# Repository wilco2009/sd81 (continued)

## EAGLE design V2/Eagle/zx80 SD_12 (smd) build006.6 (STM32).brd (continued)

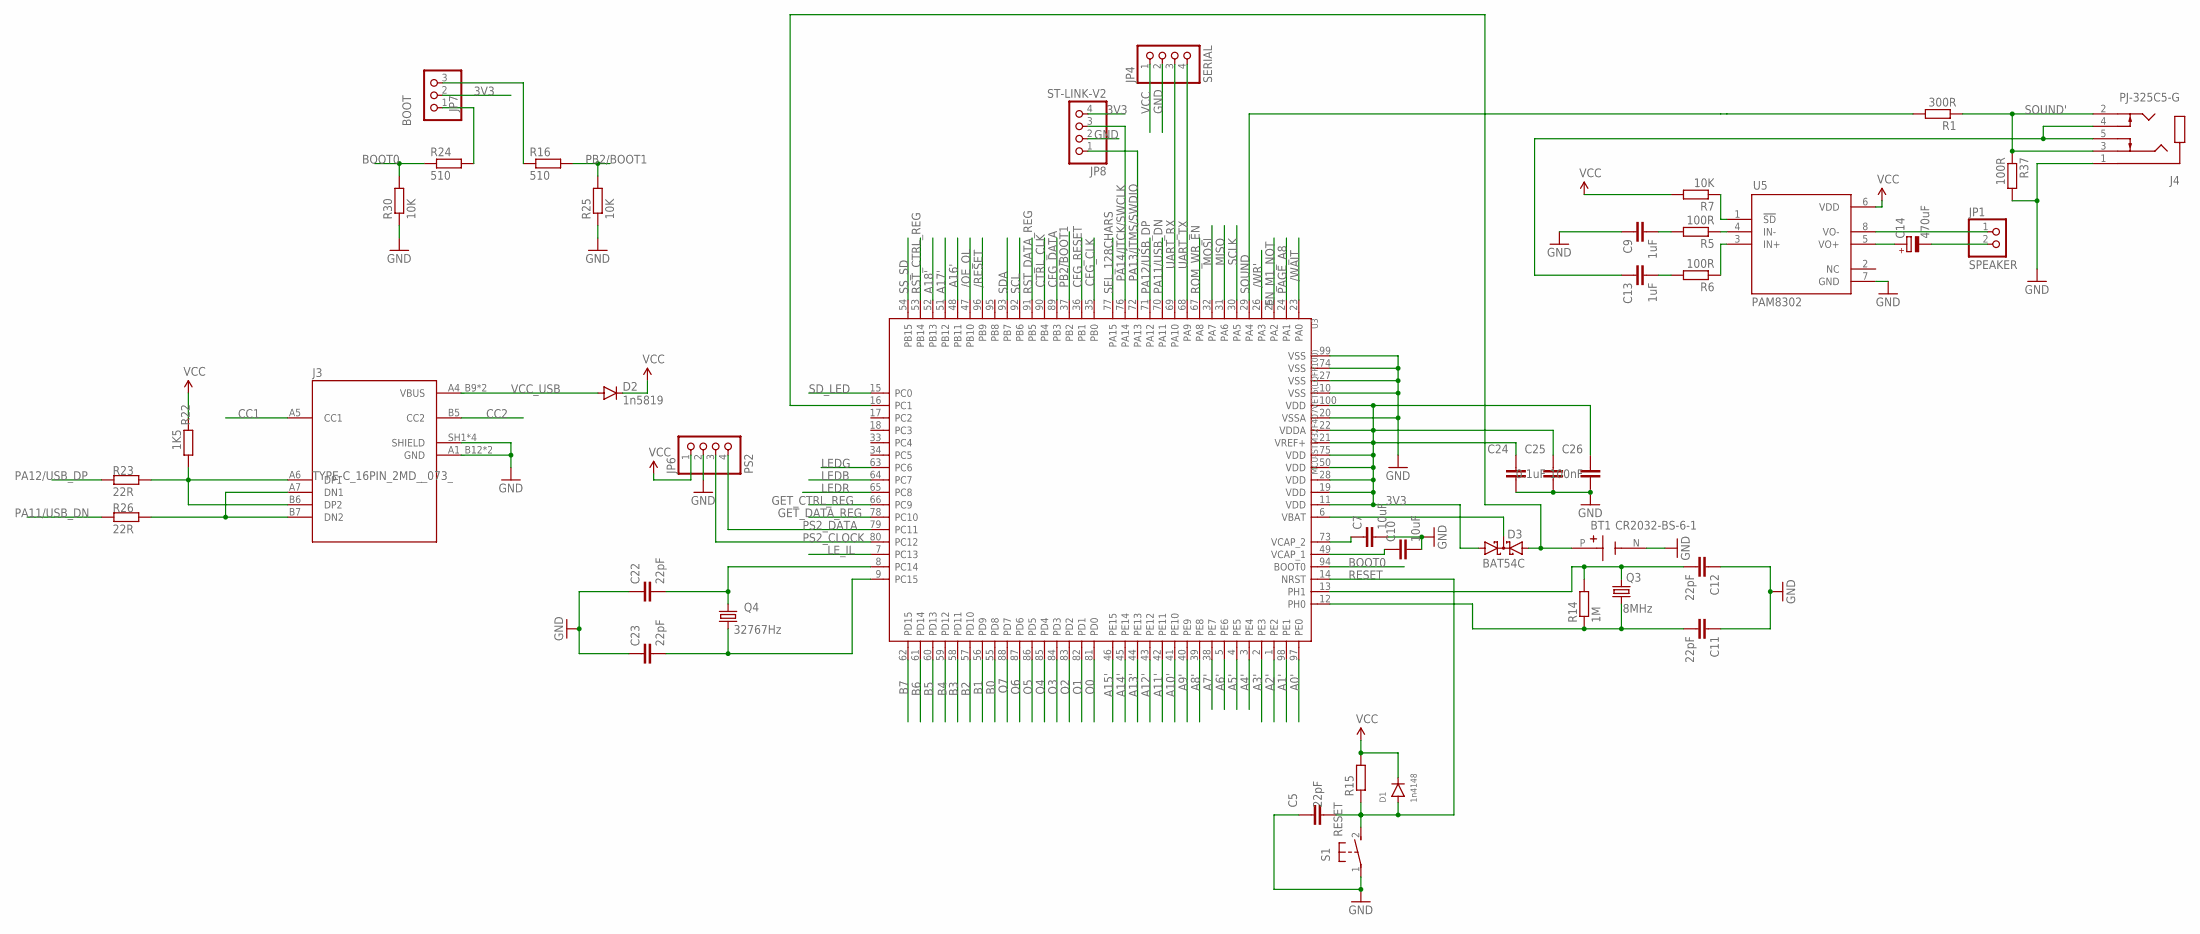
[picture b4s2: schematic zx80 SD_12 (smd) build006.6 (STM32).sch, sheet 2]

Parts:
BT1: CR2032-BS-6-1; BAT_CR2032-BS-6-1
C5, C11, C12, C22, C23: 22pF; C0603
C7, C10: 10uF; C0603
C9, C13: 1uF; C0603
C14: 470uF; UD-6,3X7,7_NICHICON
C24, C25: 0.1uF; C0603
C26: 100nF; C0603
D1: 1n4148; SOD123
D2: 1n5819; SOD323-W
D3: BAT54C; SOT23
J3: TYPE-C_16PIN_2MD__073_; SHOUHAN_TYPE-C_16PIN_2MD__073_
J4: PJ-325C5-G; XKB_PJ-325C5-G
JP1: SPEAKER; 1X02
JP4: SERIAL; 1X04
JP6: PS2; 1X04
JP7: BOOT; 1X03
JP8: ST-LINK-V2; 1X04
Q3: 8MHz; 3.2X2.5_KX-7
Q4: 32767Hz; 3.2X1.5
R1: 300R; R0603
R5, R6, R37: 100R; R0603
R7, R25, R30: 10K; R0603
R14: 1M; R0402
R15: 3k3; R0603
R16, R24: 510; R0603
R22: 1K5; R0603
R23, R26: 22R; R0603
S1: RESET; B3F-31XX
U3: MCU-STM32F407VET6(LQFP100); LQFP100-0.5-13.8X13.8MM
U5: PAM8302; SOIC127P600X170-8N

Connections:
3V3: C24.1, C25.1, C26.1, D3.1 (A1), JP7.2, JP8.4, U3.11 (VDD), U3.19 (VDD), U3.21 (VREF+), U3.22 (VDDA), U3.28 (VDD), U3.50 (VDD), U3.75 (VDD), U3.100 (VDD); also elsewhere on the board
/OE_OL: U3.47 (PB10); also elsewhere on the board
/RESET: U3.96 (PB9); also elsewhere on the board
/WAIT: U3.23 (PA0); also elsewhere on the board
/WR': U3.26 (PA3); also elsewhere on the board
A0': U3.97 (PE0); also elsewhere on the board
A1': U3.98 (PE1); also elsewhere on the board
A2': U3.1 (PE2); also elsewhere on the board
A3': U3.2 (PE3); also elsewhere on the board
A4': U3.3 (PE4); also elsewhere on the board
A5': U3.4 (PE5); also elsewhere on the board
A6': U3.5 (PE6); also elsewhere on the board
A7': U3.38 (PE7); also elsewhere on the board
A8': U3.39 (PE8); also elsewhere on the board
A9': U3.40 (PE9); also elsewhere on the board
A10': U3.41 (PE10); also elsewhere on the board
A11': U3.42 (PE11); also elsewhere on the board
A12': U3.43 (PE12); also elsewhere on the board
A13': U3.44 (PE13); also elsewhere on the board
A14': U3.45 (PE14); also elsewhere on the board
A15': U3.46 (PE15); also elsewhere on the board
A16': U3.48 (PB11); also elsewhere on the board
A17': U3.51 (PB12); also elsewhere on the board
A18': U3.52 (PB13); also elsewhere on the board
B0: U3.55 (PD8); also elsewhere on the board
B1: U3.56 (PD9); also elsewhere on the board
B2: U3.57 (PD10); also elsewhere on the board
B3: U3.58 (PD11); also elsewhere on the board
B4: U3.59 (PD12); also elsewhere on the board
B5: U3.60 (PD13); also elsewhere on the board
B6: U3.61 (PD14); also elsewhere on the board
B7: U3.62 (PD15); also elsewhere on the board
BAT: BT1.P (POS), D3.2 (A2), U3.16 (PC1)
BOOT0: R24.1, R30.2, U3.94 (BOOT0)
CC1: J3.A5 (CC1)
CC2: J3.B5 (CC2)
CFG_CLK: U3.35 (PB0); also elsewhere on the board
CFG_DATA: U3.89 (PB3); also elsewhere on the board
CFG_RESET: U3.36 (PB1); also elsewhere on the board
CTRL_CLK: U3.90 (PB4); also elsewhere on the board
EN_M1_NOT: U3.25 (PA2); also elsewhere on the board
GET_CTRL_REG: U3.66 (PC9); also elsewhere on the board
GET_DATA_REG: U3.78 (PC10); also elsewhere on the board
GND: BT1.N (NEG), C5.1, C7.2, C9.1, C10.2, C11.1, C12.1, C22.1, C23.1, C24.2, C25.2, C26.2, J3.A1_B12 (GND), J3.B1_A12 (GND), J3.SH1 (SHIELD), J3.SH2 (SHIELD), J3.SH3 (SHIELD), J3.SH4 (SHIELD), J4.1, JP4.2, JP6.2, JP8.2, R25.1, R30.1, R37.2, S1.1, U3.10 (VSS), U3.20 (VSSA), U3.27 (VSS), U3.74 (VSS), U3.99 (VSS), U5.7 (GND); also elsewhere on the board
LEDB: U3.64 (PC7); also elsewhere on the board
LEDG: U3.63 (PC6); also elsewhere on the board
LEDR: U3.65 (PC8); also elsewhere on the board
LE_IL: U3.7 (PC13); also elsewhere on the board
MISO: U3.31 (PA6); also elsewhere on the board
MOSI: U3.32 (PA7); also elsewhere on the board
unnamed: J3.A6 (DP1), J3.B6 (DP2), R22.1, R23.1
unnamed: D3.3 (CC), U3.6 (VBAT)
unnamed: R6.1, U5.3 (IN+)
unnamed: R5.1, U5.4 (IN-)
unnamed: R7.1, U5.1 (!SD)
unnamed: C7.1, U3.73 (VCAP_2)
unnamed: J3.A7 (DN1), J3.B7 (DN2), R26.1
unnamed: C9.2, R5.2
unnamed: C13.2, R6.2
unnamed: C10.1, U3.49 (VCAP_1)
unnamed: C11.2, Q3.1, R14.1, U3.12 (PH0)
unnamed: C12.2, Q3.3 (2), R14.2, U3.13 (PH1)
unnamed: JP7.3, R16.1
unnamed: JP7.1, R24.2
unnamed: C22.2, Q4.2, U3.8 (PC14)
unnamed: C23.2, Q4.1, U3.9 (PC15)
unnamed: C14.+, U5.5 (VO+)
unnamed: JP1.1, U5.8 (VO-)
unnamed: C13.1, J4.4, J4.5
unnamed: C14.-, JP1.2
O0: U3.81 (PD0); also elsewhere on the board
O1: U3.82 (PD1); also elsewhere on the board
O2: U3.83 (PD2); also elsewhere on the board
O3: U3.84 (PD3); also elsewhere on the board
O4: U3.85 (PD4); also elsewhere on the board
O5: U3.86 (PD5); also elsewhere on the board
O6: U3.87 (PD6); also elsewhere on the board
O7: U3.88 (PD7); also elsewhere on the board
PA11/USB_DN: R26.2, U3.70 (PA11)
PA12/USB_DP: R23.2, U3.71 (PA12)
PA13/JTMS/SWDIO: JP8.1, U3.72 (PA13)
PA14/JTCK/SWCLK: JP8.3, U3.76 (PA14)
PAGE_A8: U3.24 (PA1); also elsewhere on the board
PB2/BOOT1: R16.2, R25.2, U3.37 (PB2)
PS2_CLOCK: JP6.3, U3.80 (PC12)
PS2_DATA: JP6.4, U3.79 (PC11)
RESET: C5.2, D1.A, R15.1, S1.2 (S), U3.14 (NRST)
ROM_WR_EN: U3.67 (PA8); also elsewhere on the board
RST_CTRL_REG: U3.53 (PB14); also elsewhere on the board
RST_DATA_REG: U3.91 (PB5); also elsewhere on the board
SCL: U3.92 (PB6)
SCLK: U3.30 (PA5); also elsewhere on the board
SDA: U3.93 (PB7)
SD_LED: U3.15 (PC0); also elsewhere on the board
SEL_128CHARS: U3.77 (PA15); also elsewhere on the board
SOUND: R1.2, U3.29 (PA4)
SOUND': J4.2, J4.3, R1.1, R37.1; also elsewhere on the board
SS_SD: U3.54 (PB15); also elsewhere on the board
UART_RX: JP4.3, U3.69 (PA10)
UART_TX: JP4.4, U3.68 (PA9)
VCC: D1.C, D2.C, JP4.1, JP6.1, R7.2, R15.2, R22.2, U5.6 (VDD); also elsewhere on the board
VCC_USB: D2.A, J3.A4_B9 (VBUS), J3.B4_A9 (VBUS)

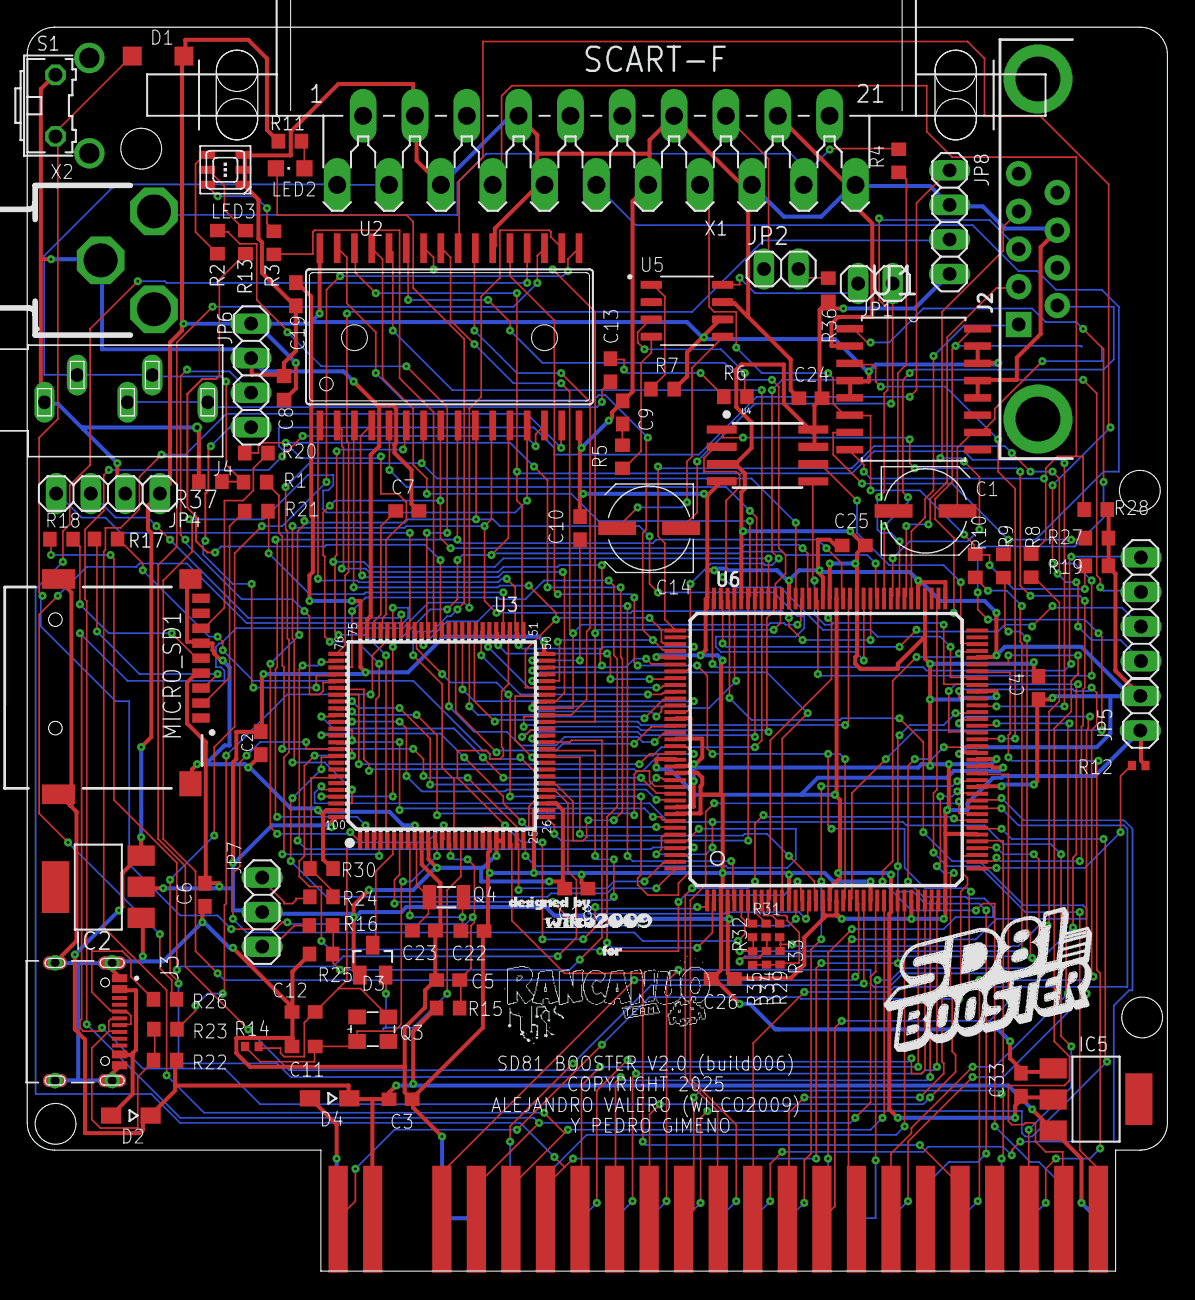
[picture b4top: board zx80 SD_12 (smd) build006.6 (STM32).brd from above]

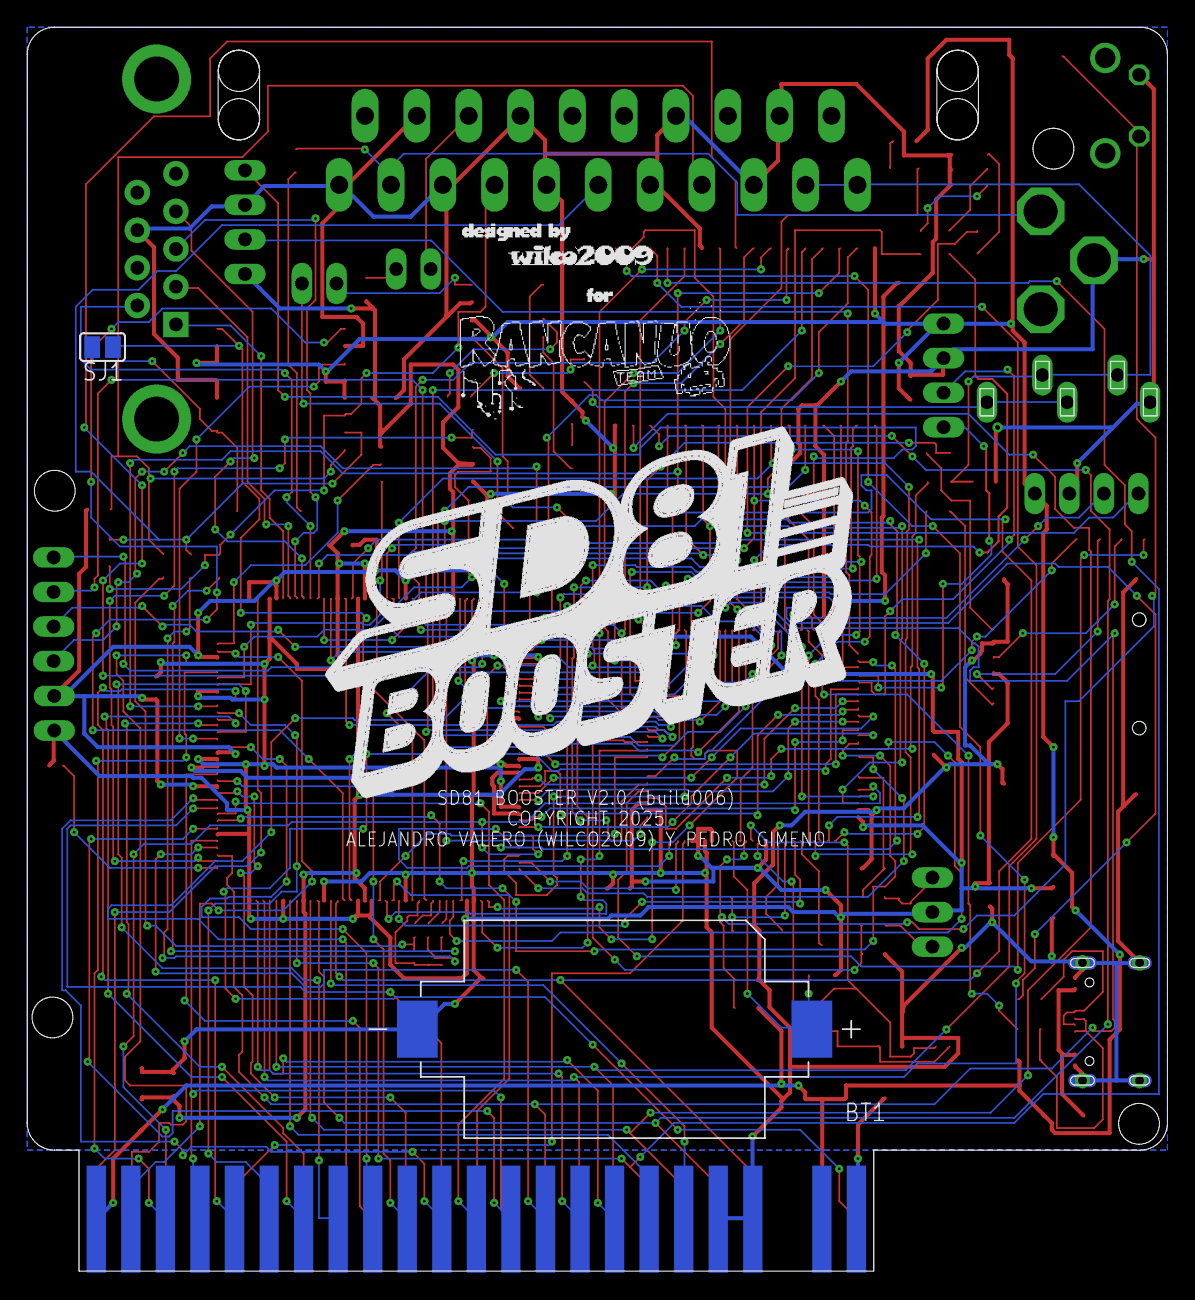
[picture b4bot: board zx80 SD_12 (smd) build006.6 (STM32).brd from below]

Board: 2 copper layers, 83.8 x 91.4 mm, 136 parts (24 on the bottom side), 174 nets.

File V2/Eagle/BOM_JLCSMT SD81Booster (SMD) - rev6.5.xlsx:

Comment | Designator | Footprint | JLCPCB Part #（optional）
220uF | C1 | SMD,D6.3xL7.7mm | C32514
100nF | C2 | C0603 | C14663
10uF | C3 | C0603 | C19702
100nF | C4 | C0603 | C14663
22pF | C5 | C0603 | C1653
10uF | C6 | C0603 | C19702
10uF | C7 | C0603 | C19702
100nF | C8 | C0603 | C14663
1uF | C9 | C0603 | C15849
10uF | C10 | C0603 | C19702
22pF | C11 | C0603 | C1653
22pF | C12 | C0603 | C1653
1uF | C13 | C0603 | C15849
470uF | C14 | SMD,D6.3xL7.7mm | C3354
100nF | C18 | C0603 | C14663
100nF | C19 | C0603 | C14663
22pF | C22 | C0603 | C1653
22pF | C23 | C0603 | C1653
100nF | C24 | C0603 | C14663
100nF | C25 | C0603 | C14663
100nF | C26 | C0603 | C14663
10uF | C33 | C0603 | C19702
1n4148 | D1 | SOD123 | C81598
1n5819 | D2 | SOD323-W | C191023
BAT54C | D3 | SOT23 | C22466350
1n5819 | D4 | SOD323-W | C191023
REG1117 | IC2 | SOT223 | C6186
1,2V | IC5 | SOT223 | C347218
JOYSTICK | J2 | DR9_MALE | C3020655
TYPE-C_16PIN_2MD__073_ | J3 | SHOUHAN_TYPE-C_16PIN_2MD__073_ | C393939
PJ-325C5-G | J4 | XKB_PJ-325C5-G | C2884942
PINH 1x02 | JP1 | 1X02 | C492401
PINH 1x02 | JP2 | 1X02 | C492401
PINH 1x04 | JP3 | 1X04
PINH 1x04 | JP4 | 1X04 | C2691448
PINH 1x02 | JP5 | 1X02
PINH 1x04 | JP6 | 1X04 | C2691448
PINH 1x03 | JP7 | 1X03 | C2937625
PINH 1x04 | JP8 | 1X04 | C2691448
SD | LED2 | CHIPLED_0805 | C2297
STATUS | LED3 | 3535-PLCC6 | C110402
TF-01A | MICRO_SD1 | TF-01A | C22383473
8MHz | Q3 | 3,2X2,5_KX-7 | C403948
32767Hz | Q4 | 3,2X1,5 | C32346
300R | R1 | R0603 | C23025
150 | R2 | R0603 | C22808
68 | R3 | R0603 | C27592
75R | R4 | R0603 | C4275
100R | R5 | R0603 | C22775
100R | R6 | R0603 | C22775
10K | R7 | R0603 | C25804
270 | R8 | R0603 | C22966
270 | R9 | R0603 | C22966
270 | R10 | R0603 | C22966
680 | R11 | R0603 | C23228
2K | R12 | R0402 | C4109
150 | R13 | R0603 | C22808
1M | R14 | R0603 | C409676
3k3 | R15 | R0603 | C22978
510 | R16 | R0603 | C23193
3k3 | R17 | R0603 | C22978
3k3 | R18 | R0603 | C22978
75R | R19 | R0603 | C4275
3k3 | R20 | R0603 | C22978
3k3 | R21 | R0603 | C22978
1K5 | R22 | R0603 | C22843
22R | R23 | R0603 | C23345
510 | R24 | R0603 | C23193
10K | R25 | R0603 | C25804
22R | R26 | R0603 | C23345
75R | R27 | R0603 | C4275
75R | R28 | R0603 | C4275
1K | R29 | R0402 | C11702
10K | R30 | R0603 | C25804
1K | R31 | R0402 | C11702
1K | R32 | R0402 | C11702
2K | R33 | R0402 | C4109
2K | R34 | R0402 | C4109
2K | R35 | R0402 | C4109
100R | R36 | R0603 | C22775
RESET | S1 | B3F-31XX | C231320
AD724 | U1 | SOIC127P1032X265-16N
AS6C4008 | U2 | SOP32-5 | C2952831
MCU-STM32F407VET6(LQFP100) | U3 | LQFP100-0,5-13,8X13,8MM | C28730
W25Q128JVSIQ | U4 | SO08-EIAJ | C97521
PAM8302 | U5 | SOIC127P600X170-8N | C112137
XC6SLX9-2TQG144C | U6 | TQ144 | C27408
SCART-F | X1 | SCART-F
CON-CONRAD_736880-2P | X2 | 3P

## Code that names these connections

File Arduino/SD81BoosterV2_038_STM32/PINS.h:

#define nWAIT           PA0
#define DEBUG_CLOCK     PA1
#define DEBUG_RDY       PA2
#define nWRb            PA3
#define DAC_PIN         PA4       // Pin PA4 para la salida DAC
#define SCLK            PA5
#define MISO            PA6
#define MOSI            PA7
#define nMEM_OEb        PA8
#define UART_TX         PA9
#define UART_RX         PA10
#define WAIT_SERIAL     PA10  // cambiar?
#define USB_DN          PA11
#define USB_DP          PA12
#define SWDIO           PA13
#define SWCLK           PA14
#define SPARE0          PA15    // connected to FPGA
//#define SEL_128CHARS  PA15

#define CFG_CLK         PB0
#define CFG_RESET       PB1
#define BOOT1           PB2
#define CFG_DATA        PB3
#define CTRL_CLK        PB4
#define RST_DATA_REG    PB5
#define FPGA_HSWAPEN    PB5
#define SCL             PB6   // unconnected
#define SDA             PB7   // unconnected
#define FPGA_RESET      PB8
#define Z80_RESET       PB9
#define nOE_OL          PB10
#define A16b            PB11 
#define A17b            PB12 
#define A18b            PB13 
#define RST_CTRL_REG    PB14
#define SEL_SPI_FLASH   PB14  // alternative use while RESET 
#define SS_SD           PB15  

#define SD_LED          PC0
#define VBAT_IN         PC1    // only as reference. see VBAT.cpp
#define FPGA_DONE       PC2
#define FPGA_CFG        PC3
#define UNUSED0         PC4
// #define QSPIN          PC5
#define SPARE2          PC5
#define ST_LED_G        PC6
#define ST_LED_B        PC7
#define ST_LED_R        PC8
#define GET_CTRL_REG    PC9
#define GET_DATA_REG    PC10
#define QSPIN           PC11     
#define PS2_CLOCK       PC12
#define PS2_DATA        PC13
#define CLK_32KH_0      PC14
#define CLK_32KH_1      PC15

#define ioLatch         GPIOD // shared
#define Data            GPIOD // shared

#define Addr            GPIOE
#define A0b             PE0
#define A1b             PE1
#define A2b             PE2
#define A3b             PE3
#define A4b             PE4
#define A5b             PE5
#define A6b             PE6
#define A7b             PE7
#define A8b             PE8
#define A9b             PE9
#define A10b            PE10
#define A11b            PE11
#define A12b            PE12
#define A13b            PE13
#define A14b            PE14
#define A15b            PE15

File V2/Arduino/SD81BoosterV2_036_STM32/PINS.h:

#define ioLatch        GPIOD
#define VBAT_IN        PC1    // only as reference. see VBAT.cpp
#define ST_LED_R       PC8
#define ST_LED_B       PC7
#define ST_LED_G       PC6
#define DEBUG_RDY      PC13
#define FPGA_RESET      PB9
//#define nMEM_LATCH_OE  7
//#define TMS            8
//#define TDI            9
//#define TDO           10
//#define TCK           11
//#define VREF          12
#define RST_CTRL_REG  PB14
#define CTRL_CLK      PB4
#define RST_DATA_REG  PB5
#define GET_CTRL_REG  PC9
#define GET_DATA_REG  PC10
#define nOE_OL        PB10
#define A16b          PB11 
#define A17b          PB12 
#define A18b          PB13 
#define A15b          PE15
#define A14b          PE14
#define A13b          PE13
#define A12b          PE12
#define A11b          PE11
#define A10b          PE10
#define A9b           PE9
#define A8b           PE8
#define A7b           PE7
#define A6b           PE6
#define A5b           PE5
#define A4b           PE4
#define A3b           PE3
#define A2b           PE2
#define A1b           PE1
#define A0b           PE0
//#define nMEM_CE       38
//#define ALE           39
//#define nMEM_OE       40
#define nWAIT         PA0
//#define FULLPAGING    PA1
#define DEBUG_CLOCK   PA1
#define EN_M1_NOT     PA2
#define nWRb          PA3

#define SD_LED        PC0
//#define INT_CHR_TABLE 48
#define SEL_128CHARS  PA15
#define MISO          PA6
#define MOSI          PA7
#define SCLK          PA5
#define SS_SD         PB15  

#define SDA           PB7
#define SCL           PB6

#define CFG_DATA      PB3
#define CFG_RESET     PB1
#define CFG_CLK       PB0

// NOT USED?
#define ROM_WR_EN     PA8 
#define PS2_DATA      PC11
#define PS2_CLOCK     PC12

// CAMBIAR CON NUEVA VERSION
#define WAIT_SERIAL  PA10  // cambiar?
// #define FPGA_M0      PC12  // poner a 1 en el reset  (A4) PS2DATA NARANJA
// #define FPGA_M1      PC11  // poner a 0 en el reset  (A8) PS2CLOCK ROJO
#define Z80_RESET   PC11
#define FPGA_HSWAPEN PB5

// #define OUTPUT_LATCH  PORTD         
// #define INPUT_LATCH   PIND >> 8

// SINONIMOS
#define nMEM_OEb       PA8
#define Data           GPIOD
#define Addr           GPIOE

#define QSPIN          PC12 // Buscar pin libre


//#define D0            22
//#define D1            23
//#define D2            24
//#define D3            25
//#define D4            26
//#define D5            27
//#define D6            28
//#define D7            29

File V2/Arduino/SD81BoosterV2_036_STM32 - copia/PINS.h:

#define ioLatch        GPIOD
#define ST_LED_R       PC8
#define ST_LED_B       PC7
#define ST_LED_G       PC6
#define LE_IL          PC13
#define Z80_RESET      PB9
//#define nMEM_LATCH_OE  7
//#define TMS            8
//#define TDI            9
//#define TDO           10
//#define TCK           11
//#define VREF          12
#define RST_CTRL_REG  PB14
#define CTRL_CLK      PB4
#define RST_DATA_REG  PB5
#define GET_CTRL_REG  PC9
#define GET_DATA_REG  PC10
#define nOE_OL        PB10
#define A16b          PB11 
#define A17b          PB12 
#define A18b          PB13 
#define A15b          PE15
#define A14b          PE14
#define A13b          PE13
#define A12b          PE12
#define A11b          PE11
#define A10b          PE10
#define A9b           PE9
#define A8b           PE8
#define A7b           PE7
#define A6b           PE6
#define A5b           PE5
#define A4b           PE4
#define A3b           PE3
#define A2b           PE2
#define A1b           PE1
#define A0b           PE0
//#define nMEM_CE       38
//#define ALE           39
//#define nMEM_OE       40
#define nWRb          PC0
#define nWAIT         PA0
#define FULLPAGING    PA1
#define EN_M1_NOT     PA2
//#define SPEAKER       45
//#define STD_48K       46
#define SD_LED        PC0
//#define INT_CHR_TABLE 48
#define SEL_128CHARS  PA15
#define MISO          PA6
#define MOSI          PA7
#define SCLK          PA5
#define SS_SD         PB15  

#define SDA           PB7
#define SCL           PB6

#define OUTPUT_LATCH  PORTD         
#define INPUT_LATCH   PIND >> 8

// SINONIMOS
#define nMEM_OE       PA1
#define nMEM_CE       PA2
#define Data           GPIOD
#define Addr           GPIOE

//#define D0            22
//#define D1            23
//#define D2            24
//#define D3            25
//#define D4            26
//#define D5            27
//#define D6            28
//#define D7            29

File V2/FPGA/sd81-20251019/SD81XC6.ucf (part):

#PACE: Start of Constraints generated by PACE
#PACE: Start of PACE I/O Pin Assignments

//NET "LE_OL"  LOC = "P72"  ; 				//
//NET "nOE_CTRL_CLOCK"  LOC = "P10"  ; 	//
//NET "nOE_IL"  LOC = "P15"  ; 				//

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//
NET "nRST_CTRL_REG" LOC = P1;
//
NET "GET_DATA_REG" LOC = P2;
// NET "GND"  			LOC = "P3"  ; 				//
// NET "3V3"  			LOC = "P4"  ; 				//
//
NET "GET_CTRL_REG" LOC = P5;
//
NET "CTRL_CLK" LOC = P6;
//
NET "VRED" LOC = P7;
//
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//
NET "VBLUE" LOC = P9;
//
NET "CSYNC" LOC = P10;
//
NET "BRIGHT" LOC = P11;
//
NET "nOE_OL" LOC = P12;
// NET "GND"  			LOC = "P13" ; 				//
//
NET "DEBUG_RDY" LOC = P14;
NET "CFG_DATA" LOC = P15;
//
NET "CFG_RESET" LOC = P16;
//
NET "CFG_CLK" LOC = P17;
// NET "3V3"  			LOC = "P18" ; 				//
// NET "1V2"  			LOC = "P19" ; 				//
// NET "3V3"  			LOC = "P20" ; 				//
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NET "A2" LOC = P35;
// NET "3V3"  			LOC = "P36" ; 				//
// NET "PROGRAM B2"	LOC = "P37" ; 				//
// NET "FLASH_CS"  		LOC = "P38" ; 				//
//
NET "D4" LOC = P39;
//
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//
NET "A7" LOC = P62;
// NET "3V3"  			LOC = "P63" ; 				//
//NET "FLASH_MOSI"  	LOC = "P64" ; 				//
//NET "FLASH_MISO"  	LOC = "P65" ; 				//
//
NET "A5" LOC = P66;
//
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// NET "GND"  			LOC = "P68" ; 				//
//
NET "A4" LOC = P69;
//NET "FLASH_SCLK"  	LOC = "P70" ; 				//
// NET "DONE"  		LOC = "P71" ; 				//
// NET "CMPCS_B"		LOC = "P72" ; 				//
// NET "GND"  			LOC = "P73" ; 				//
//
NET "nRFSH" LOC = P74;
//NET "ROMCS"  			LOC = "P75" ; 				//
// NET "3V3"  			LOC = "P76" ; 				//
// NET "GND"  			LOC = "P77" ; 				//
//
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//
NET "RIGHT" LOC = P81;
//
NET "FIRE" LOC = P82;
//
NET "A0x" LOC = P83;
//
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//
NET "nRESET" LOC = P139;
//
NET "SEL_128CHARS" LOC = P141;
//
NET "nMEM_OEm" LOC = P142;
//
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NET "B5" DRIVE = 12;
NET "B6" DRIVE = 12;
NET "B7" DRIVE = 12;
NET "BRIGHT" DRIVE = 12;
NET "CFG_CLK" DRIVE = 12;
NET "CFG_DATA" DRIVE = 12;
NET "CFG_RESET" DRIVE = 12;
NET "CSYNC" DRIVE = 12;
NET "CTRL_CLK" DRIVE = 12;
NET "D0" DRIVE = 12;
NET "D1" DRIVE = 12;
NET "D2" DRIVE = 12;
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NET "D6" DRIVE = 12;
NET "D7" DRIVE = 12;
NET "DOWN" DRIVE = 12;
NET "FIRE" DRIVE = 12;
NET "FULL_PAGING" DRIVE = 12;
NET "GET_CTRL_REG" DRIVE = 12;
NET "GET_DATA_REG" DRIVE = 12;
NET "LEFT" DRIVE = 12;
NET "nCLOCK" DRIVE = 12;
NET "nHALT" DRIVE = 12;
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NET "test1" DRIVE = 12;
NET "RIGHT" DRIVE = 12;
NET "nMEM_OEm" DRIVE = 12;
NET "SEL_128CHARS" DRIVE = 12;
NET "UP" DRIVE = 12;
NET "VBLUE" DRIVE = 12;
NET "VGREEN" DRIVE = 12;
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
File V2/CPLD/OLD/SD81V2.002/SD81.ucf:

#PACE: Start of Constraints generated by PACE

#PACE: Start of PACE I/O Pin Assignments
NET "D0"  LOC = "P18"  ; 					//
NET "D1"  LOC = "P19"  ; 					//
NET "D2"  LOC = "P20"  ; 					//
NET "D3"  LOC = "P29"  ; 					//
NET "D4"  LOC = "P32"  ; 					//
NET "D5"  LOC = "P25"  ; 					//
NET "D6"  LOC = "P23"  ; 					//
NET "D7"  LOC = "P16"  ; 					//

NET "A0"  LOC = "P24"  ;					//
NET "A1"  LOC = "P28"  ; 					//
NET "A2"  LOC = "P30"  ; 					//
NET "A3"  LOC = "P33"  ; 					//
NET "A4"  LOC = "P63"  ; 					//
NET "A5"  LOC = "P60"  ; 					//
NET "A6"  LOC = "P34"  ; 					//
NET "A7"  LOC = "P58"  ; 					//
NET "A8"  LOC = "P55"  ; 					//
NET "A9"  LOC = "P53"  ; 					//
NET "A10"  LOC = "P50"  ; 					//
NET "A11"  LOC = "P46"  ; 					//
NET "A12"  LOC = "P42"  ; 					//
NET "A13"  LOC = "P40"  ; 					//
NET "A14"  LOC = "P37"  ; 					//
NET "A15"  LOC = "P35"  ; 					//

NET "A0x"  LOC = "P2"  ; 					//
NET "A1x"  LOC = "P87"  ; 					//
NET "A2x"  LOC = "P89"  ; 					//
NET "A3x"  LOC = "P90"  ; 					//
NET "A4x"  LOC = "P91"  ; 					//
NET "A5x"  LOC = "P92"  ; 					//
NET "A6x"  LOC = "P93"  ; 					//
NET "A7x"  LOC = "P94"  ; 					//
NET "A8x"  LOC = "P95"  ; 					//
NET "A9x"  LOC = "P96"  ; 					//
NET "A10x"  LOC = "P3"  ; 					//
NET "A11x"  LOC = "P4"  ; 					//
NET "A12x"  LOC = "P1"  ; 					//
NET "A13x"  LOC = "P99"  ; 				//
NET "A14x"  LOC = "P11"  ;					// 
NET "A15x"  LOC = "P6"  ; 					//
NET "A16x"  LOC = "P7"  ; 					//
NET "A17x"  LOC = "P8"  ; 					//
NET "A18x"  LOC = "P9"  ; 					//

NET "nMEM_OE"  LOC = "P12"  ; 			//
NET "nMEM_CE"  LOC = "P97"  ; 			//
NET "nRST_CTRL_REG"  LOC = "P82"  ; 	//
NET "nRST_DATA_REG"  LOC = "P81"  ; 	//
NET "GET_CTRL_REG"  LOC = "P86"  ; 		//
NET "GET_DATA_REG"  LOC = "P85"  ; 		//
NET "nIORQ"  LOC = "P43"  ;				// 
NET "LE_OL"  LOC = "P72"  ; 				//
NET "nM1"  LOC = "P61"  ; 					//
NET "nMREQ"  LOC = "P41"  ; 				//
NET "nOE_CTRL_CLOCK"  LOC = "P10"  ; 	//
NET "nOE_IL"  LOC = "P15"  ; 				//
NET "nOE_RAMCS"  LOC = "P17"  ; 			//
NET "nOE_ROMCS"  LOC = "P14"  ; 			//
NET "FULL_PAGING"  LOC = "P80"  ; 			//
NET "SEL_128CHARS"  LOC = "P78"  ; 		//
NET "nRD"  LOC = "P49"  ; 					//
NET "nRFSH"  LOC = "P64"  ; 				//
NET "nRESET"  LOC = "P71"  ; 				//
NET "nWAIT"  LOC = "P56"  ; 				//
NET "nHALT"  LOC = "P39"  ; 				//
NET "nNMI"  LOC = "P36"  ;					// 
NET "nBUSRQ"  LOC = "P59"  ; 				//
NET "nBUSAK"  LOC = "P54"  ; 				//
NET "nWR"  LOC = "P52"  ; 					//
NET "nWRx"  LOC = "P13"  ;					// 
NET "nCLOCK"  LOC = "P22"  ; 				//

NET "SPARE1"  LOC = "P74"  ; 				//
NET "SPARE2"  LOC = "P76"  ; 				//
NET "SPARE3"  LOC = "P77"  ; 				//
NET "ROM_WR_EN"  LOC = "P79"  ; 				//

#PACE: Start of PACE Area Constraints

#PACE: Start of PACE Prohibit Constraints

#PACE: End of Constraints generated by PACE

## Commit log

2026-05-04 Primer commit: inicialización del proyecto
2026-05-05 Remove Updates/ and CLAUDE.md from tracking (gitignored)
2026-05-05 Clean repo: gitignore Eagle non-sources, Updates/, CLAUDE.md
2026-05-05 Clean repo: remove build artifacts, bak folders and untracked files from index
